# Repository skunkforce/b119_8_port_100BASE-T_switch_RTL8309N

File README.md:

# edgy_board number b119
This design is part of the [edgy board project](https://github.com/skunkforce/edgy_boards). It provides a cheap 8-port 100BASE-T switch.

# getting started
This repository uses submodules. After cloning use the command 

```$ git submodule update --init --recursive```

to pull the submodules before opening the project with kicad. 

# Tests
Tests can be found in [TESTS.md](TESTS.md)

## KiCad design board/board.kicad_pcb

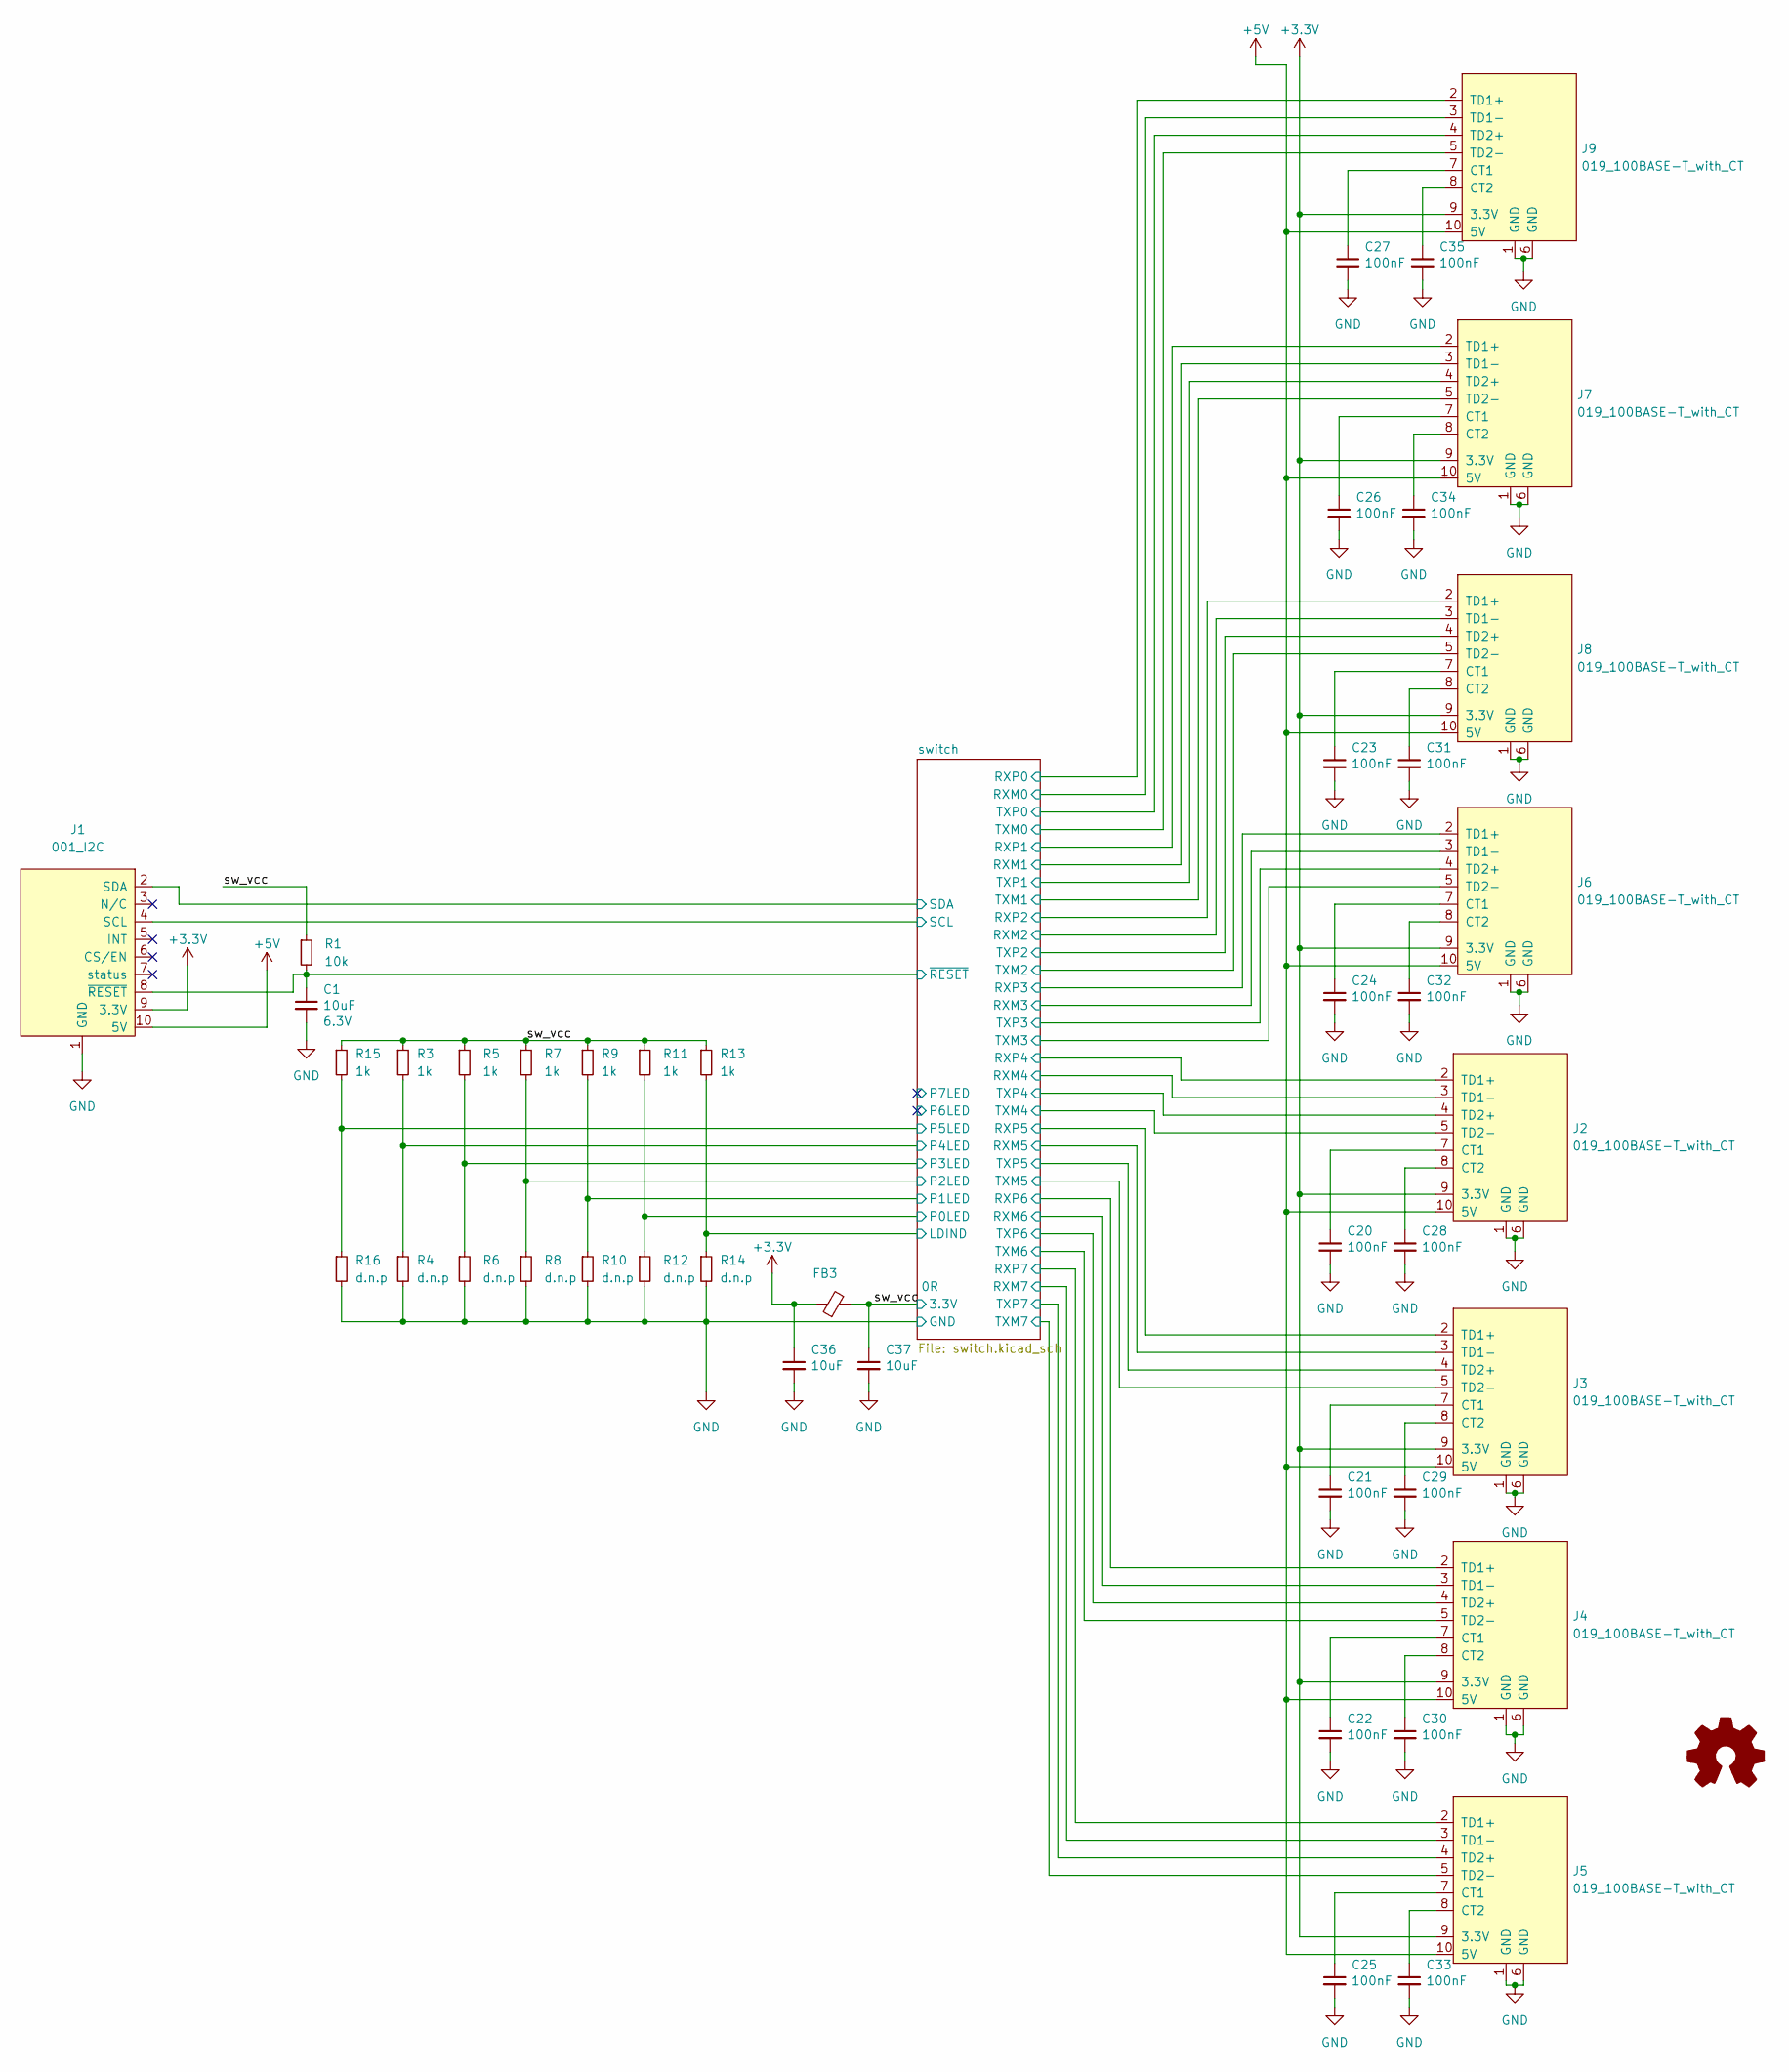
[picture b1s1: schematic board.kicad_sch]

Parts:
C1: 10uF; C_0402_1005Metric; Voltage 6.3V; MPN CL05A105MP5NNNC; Digi-Key_PN 1276-1448-1-ND
C20, C21, C22, C23, C24, C25, C26, C27, C28, C29, C30, C31, C32, C33, C34, C35: 100nF; C_0603_1608Metric; lcsc C14663
C36, C37: 10uF; C_0402_1005Metric; lcsc C15525
FB3: 0R; L_0603_1608Metric; MPN 74279228111; lcsc C21189
J1: 001_I2C; on_edge_2x05_device
J2, J3, J4, J5, J6, J7, J8, J9: 019_100BASE-T_with_CT; on_edge_2x05_host
LOGO1: Logo_Open_Hardware_Small; OSHW-Symbol_6.7x6mm_SilkScreen
R1: 10k; R_0402_1005Metric; lcsc C25744
R3, R5, R7, R9, R11, R13, R15: 1k; R_0402_1005Metric; lcsc C11702
R4, R6, R8, R10, R12, R14, R16: d.n.p; R_0402_1005Metric

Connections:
+3.3V: C36.1, FB3.1, J1.9 (3.3V), J2.9 (3.3V), J3.9 (3.3V), J4.9 (3.3V), J5.9 (3.3V), J6.9 (3.3V), J7.9 (3.3V), J8.9 (3.3V), J9.9 (3.3V)
+5V: J1.10 (5V), J2.10 (5V), J3.10 (5V), J4.10 (5V), J5.10 (5V), J6.10 (5V), J7.10 (5V), J8.10 (5V), J9.10 (5V)
/sw_vcc: C37.1, FB3.2, R1.1, R3.1, R5.1, R7.1, R9.1, R11.1, R13.1, R15.1; also elsewhere on the board
/switch/LDIND: R13.2, R14.1; also elsewhere on the board
/switch/P0LED: R11.2, R12.1; also elsewhere on the board
/switch/P1LED: R9.2, R10.1; also elsewhere on the board
/switch/P2LED: R7.2, R8.1; also elsewhere on the board
/switch/P3LED: R5.2, R6.1; also elsewhere on the board
/switch/P4LED: R3.2, R4.1; also elsewhere on the board
/switch/P5LED: R15.2, R16.1; also elsewhere on the board
/switch/RXM0: J9.3 (TD1-); also elsewhere on the board
/switch/RXM1: J7.3 (TD1-); also elsewhere on the board
/switch/RXM2: J8.3 (TD1-); also elsewhere on the board
/switch/RXM3: J6.3 (TD1-); also elsewhere on the board
/switch/RXM4: J2.3 (TD1-); also elsewhere on the board
/switch/RXM5: J3.3 (TD1-); also elsewhere on the board
/switch/RXM6: J4.3 (TD1-); also elsewhere on the board
/switch/RXM7: J5.3 (TD1-); also elsewhere on the board
/switch/RXP0: J9.2 (TD1+); also elsewhere on the board
/switch/RXP1: J7.2 (TD1+); also elsewhere on the board
/switch/RXP2: J8.2 (TD1+); also elsewhere on the board
/switch/RXP3: J6.2 (TD1+); also elsewhere on the board
/switch/RXP4: J2.2 (TD1+); also elsewhere on the board
/switch/RXP5: J3.2 (TD1+); also elsewhere on the board
/switch/RXP6: J4.2 (TD1+); also elsewhere on the board
/switch/RXP7: J5.2 (TD1+); also elsewhere on the board
/switch/SCL: J1.4 (SCL); also elsewhere on the board
/switch/SDA: J1.2 (SDA); also elsewhere on the board
/switch/TXM0: J9.5 (TD2-); also elsewhere on the board
/switch/TXM1: J7.5 (TD2-); also elsewhere on the board
/switch/TXM2: J8.5 (TD2-); also elsewhere on the board
/switch/TXM3: J6.5 (TD2-); also elsewhere on the board
/switch/TXM4: J2.5 (TD2-); also elsewhere on the board
/switch/TXM5: J3.5 (TD2-); also elsewhere on the board
/switch/TXM6: J4.5 (TD2-); also elsewhere on the board
/switch/TXM7: J5.5 (TD2-); also elsewhere on the board
/switch/TXP0: J9.4 (TD2+); also elsewhere on the board
/switch/TXP1: J7.4 (TD2+); also elsewhere on the board
/switch/TXP2: J8.4 (TD2+); also elsewhere on the board
/switch/TXP3: J6.4 (TD2+); also elsewhere on the board
/switch/TXP4: J2.4 (TD2+); also elsewhere on the board
/switch/TXP5: J3.4 (TD2+); also elsewhere on the board
/switch/TXP6: J4.4 (TD2+); also elsewhere on the board
/switch/TXP7: J5.4 (TD2+); also elsewhere on the board
/switch/~RESET: C1.1, J1.8 (~RESET), R1.2; also elsewhere on the board
GND: C1.2, C20.2, C21.2, C22.2, C23.2, C24.2, C25.2, C26.2, C27.2, C28.2, C29.2, C30.2, C31.2, C32.2, C33.2, C34.2, C35.2, C36.2, C37.2, J1.1 (GND), J2.1 (GND), J2.6 (GND), J3.1 (GND), J3.6 (GND), J4.1 (GND), J4.6 (GND), J5.1 (GND), J5.6 (GND), J6.1 (GND), J6.6 (GND), J7.1 (GND), J7.6 (GND), J8.1 (GND), J8.6 (GND), J9.1 (GND), J9.6 (GND), R4.2, R6.2, R8.2, R10.2, R12.2, R14.2, R16.2; also elsewhere on the board
unnamed: C20.1, J2.7 (CT1)
unnamed: C28.1, J2.8 (CT2)
unnamed: C21.1, J3.7 (CT1)
unnamed: C29.1, J3.8 (CT2)
unnamed: C22.1, J4.7 (CT1)
unnamed: C30.1, J4.8 (CT2)
unnamed: C25.1, J5.7 (CT1)
unnamed: C33.1, J5.8 (CT2)
unnamed: C24.1, J6.7 (CT1)
unnamed: C32.1, J6.8 (CT2)
unnamed: C26.1, J7.7 (CT1)
unnamed: C34.1, J7.8 (CT2)
unnamed: C23.1, J8.7 (CT1)
unnamed: C31.1, J8.8 (CT2)
unnamed: C27.1, J9.7 (CT1)
unnamed: C35.1, J9.8 (CT2)

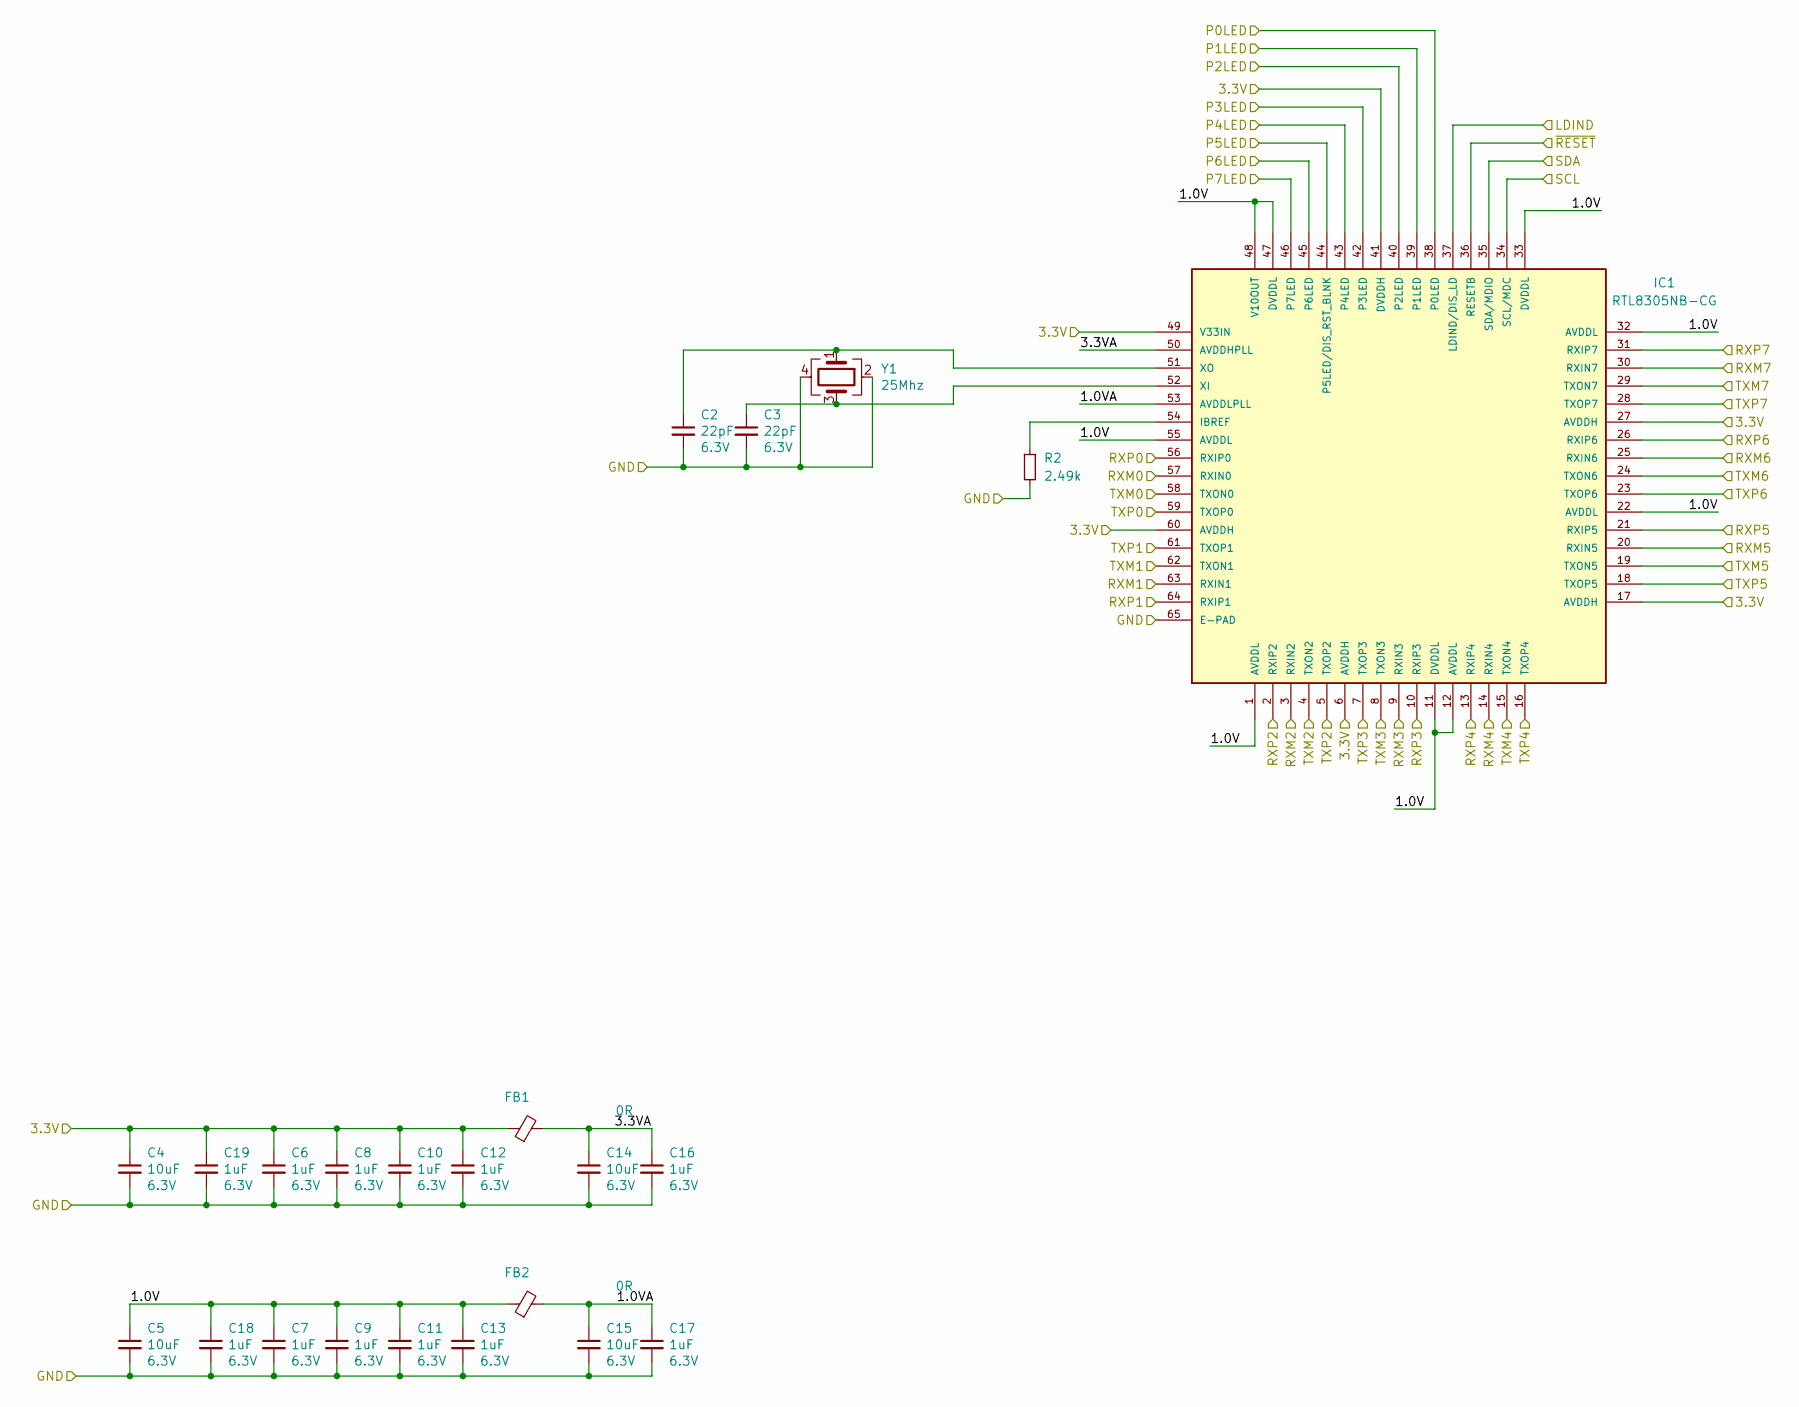
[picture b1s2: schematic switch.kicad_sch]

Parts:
C2, C3: 22pF; C_0402_1005Metric; Voltage 6.3V; Digi-Key_PN 1276-1665-1-ND
C4, C5, C14, C15: 10uF; C_0402_1005Metric; Voltage 6.3V; MPN CL05A105MP5NNNC; Digi-Key_PN 1276-1448-1-ND
C6, C7, C8, C9, C10, C11, C12, C13, C16, C17, C18, C19: 1uF; C_0402_1005Metric; Voltage 6.3V; MPN CL05A105MP5NNNC; Digi-Key_PN 1276-1448-1-ND
FB1, FB2: 0R; L_0603_1608Metric; MPN 74279228111; lcsc C21189
IC1: RTL8305NB-CG; QFN-64-1EP_9x9mm_P0.5mm_EP6x6mm; lcsc C52146
R2: 2.49k; R_0402_1005Metric; lcsc C25884
Y1: 25Mhz; Crystal_SMD_2520-4Pin_2.5x2.0mm; MPN ECS-250-18-36B-CKY-TR; lcsc C9006

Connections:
/sw_vcc: C4.1, C6.1, C8.1, C10.1, C12.1, C19.1, FB1.1, IC1.6 (AVDDH), IC1.17 (AVDDH), IC1.27 (AVDDH), IC1.41 (DVDDH), IC1.49 (V33IN), IC1.60 (AVDDH); also elsewhere on the board
/switch/1.0V: C5.1, C7.1, C9.1, C11.1, C13.1, C18.1, FB2.1, IC1.1 (AVDDL), IC1.11 (DVDDL), IC1.12 (AVDDL), IC1.22 (AVDDL), IC1.32 (AVDDL), IC1.33 (DVDDL), IC1.47 (DVDDL), IC1.48 (V10OUT), IC1.55 (AVDDL)
/switch/1.0VA: C15.1, C17.1, FB2.2, IC1.53 (AVDDLPLL)
/switch/3.3VA: C14.1, C16.1, FB1.2, IC1.50 (AVDDHPLL)
/switch/LDIND: IC1.37 (LDIND/DIS_LD); also elsewhere on the board
/switch/P0LED: IC1.38 (P0LED); also elsewhere on the board
/switch/P1LED: IC1.39 (P1LED); also elsewhere on the board
/switch/P2LED: IC1.40 (P2LED); also elsewhere on the board
/switch/P3LED: IC1.42 (P3LED); also elsewhere on the board
/switch/P4LED: IC1.43 (P4LED); also elsewhere on the board
/switch/P5LED: IC1.44 (P5LED/DIS_RST_BLNK); also elsewhere on the board
/switch/P6LED: IC1.45 (P6LED)
/switch/P7LED: IC1.46 (P7LED)
/switch/RXM0: IC1.57 (RXIN0); also elsewhere on the board
/switch/RXM1: IC1.63 (RXIN1); also elsewhere on the board
/switch/RXM2: IC1.3 (RXIN2); also elsewhere on the board
/switch/RXM3: IC1.9 (RXIN3); also elsewhere on the board
/switch/RXM4: IC1.14 (RXIN4); also elsewhere on the board
/switch/RXM5: IC1.20 (RXIN5); also elsewhere on the board
/switch/RXM6: IC1.25 (RXIN6); also elsewhere on the board
/switch/RXM7: IC1.30 (RXIN7); also elsewhere on the board
/switch/RXP0: IC1.56 (RXIP0); also elsewhere on the board
/switch/RXP1: IC1.64 (RXIP1); also elsewhere on the board
/switch/RXP2: IC1.2 (RXIP2); also elsewhere on the board
/switch/RXP3: IC1.10 (RXIP3); also elsewhere on the board
/switch/RXP4: IC1.13 (RXIP4); also elsewhere on the board
/switch/RXP5: IC1.21 (RXIP5); also elsewhere on the board
/switch/RXP6: IC1.26 (RXIP6); also elsewhere on the board
/switch/RXP7: IC1.31 (RXIP7); also elsewhere on the board
/switch/SCL: IC1.34 (SCL/MDC); also elsewhere on the board
/switch/SDA: IC1.35 (SDA/MDIO); also elsewhere on the board
/switch/TXM0: IC1.58 (TXON0); also elsewhere on the board
/switch/TXM1: IC1.62 (TXON1); also elsewhere on the board
/switch/TXM2: IC1.4 (TXON2); also elsewhere on the board
/switch/TXM3: IC1.8 (TXON3); also elsewhere on the board
/switch/TXM4: IC1.15 (TXON4); also elsewhere on the board
/switch/TXM5: IC1.19 (TXON5); also elsewhere on the board
/switch/TXM6: IC1.24 (TXON6); also elsewhere on the board
/switch/TXM7: IC1.29 (TXON7); also elsewhere on the board
/switch/TXP0: IC1.59 (TXOP0); also elsewhere on the board
/switch/TXP1: IC1.61 (TXOP1); also elsewhere on the board
/switch/TXP2: IC1.5 (TXOP2); also elsewhere on the board
/switch/TXP3: IC1.7 (TXOP3); also elsewhere on the board
/switch/TXP4: IC1.16 (TXOP4); also elsewhere on the board
/switch/TXP5: IC1.18 (TXOP5); also elsewhere on the board
/switch/TXP6: IC1.23 (TXOP6); also elsewhere on the board
/switch/TXP7: IC1.28 (TXOP7); also elsewhere on the board
/switch/~RESET: IC1.36 (RESETB); also elsewhere on the board
GND: C2.2, C3.2, C4.2, C5.2, C6.2, C7.2, C8.2, C9.2, C10.2, C11.2, C12.2, C13.2, C14.2, C15.2, C16.2, C17.2, C18.2, C19.2, IC1.65 (E-PAD), R2.2, Y1.2, Y1.4; also elsewhere on the board
unnamed: IC1.54 (IBREF), R2.1
unnamed: C3.1, IC1.52 (XI), Y1.3
unnamed: C2.1, IC1.51 (XO), Y1.1

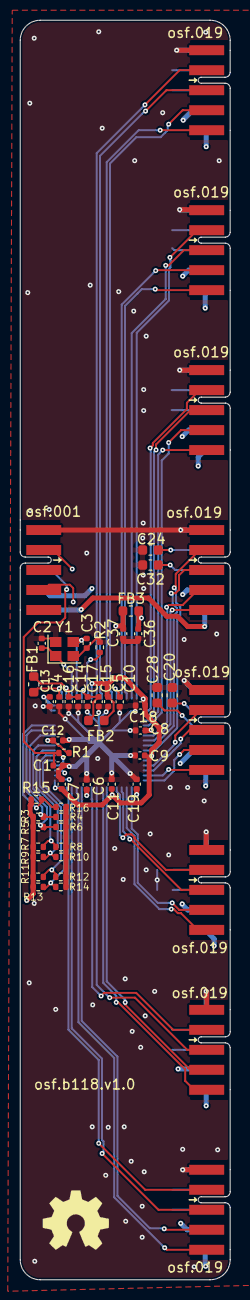
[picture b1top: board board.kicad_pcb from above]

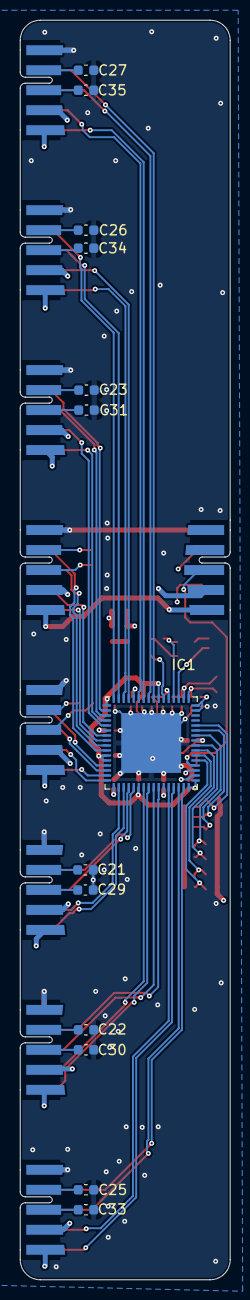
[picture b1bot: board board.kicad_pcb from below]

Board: 4 copper layers, 21.0 x 126.0 mm, 68 parts (13 on the bottom side), 68 nets.

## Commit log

2023-03-29 added decoupling components
2023-03-30 added N filter for input voltage
2024-01-30 added lcsc numbers and updated I2C connector
